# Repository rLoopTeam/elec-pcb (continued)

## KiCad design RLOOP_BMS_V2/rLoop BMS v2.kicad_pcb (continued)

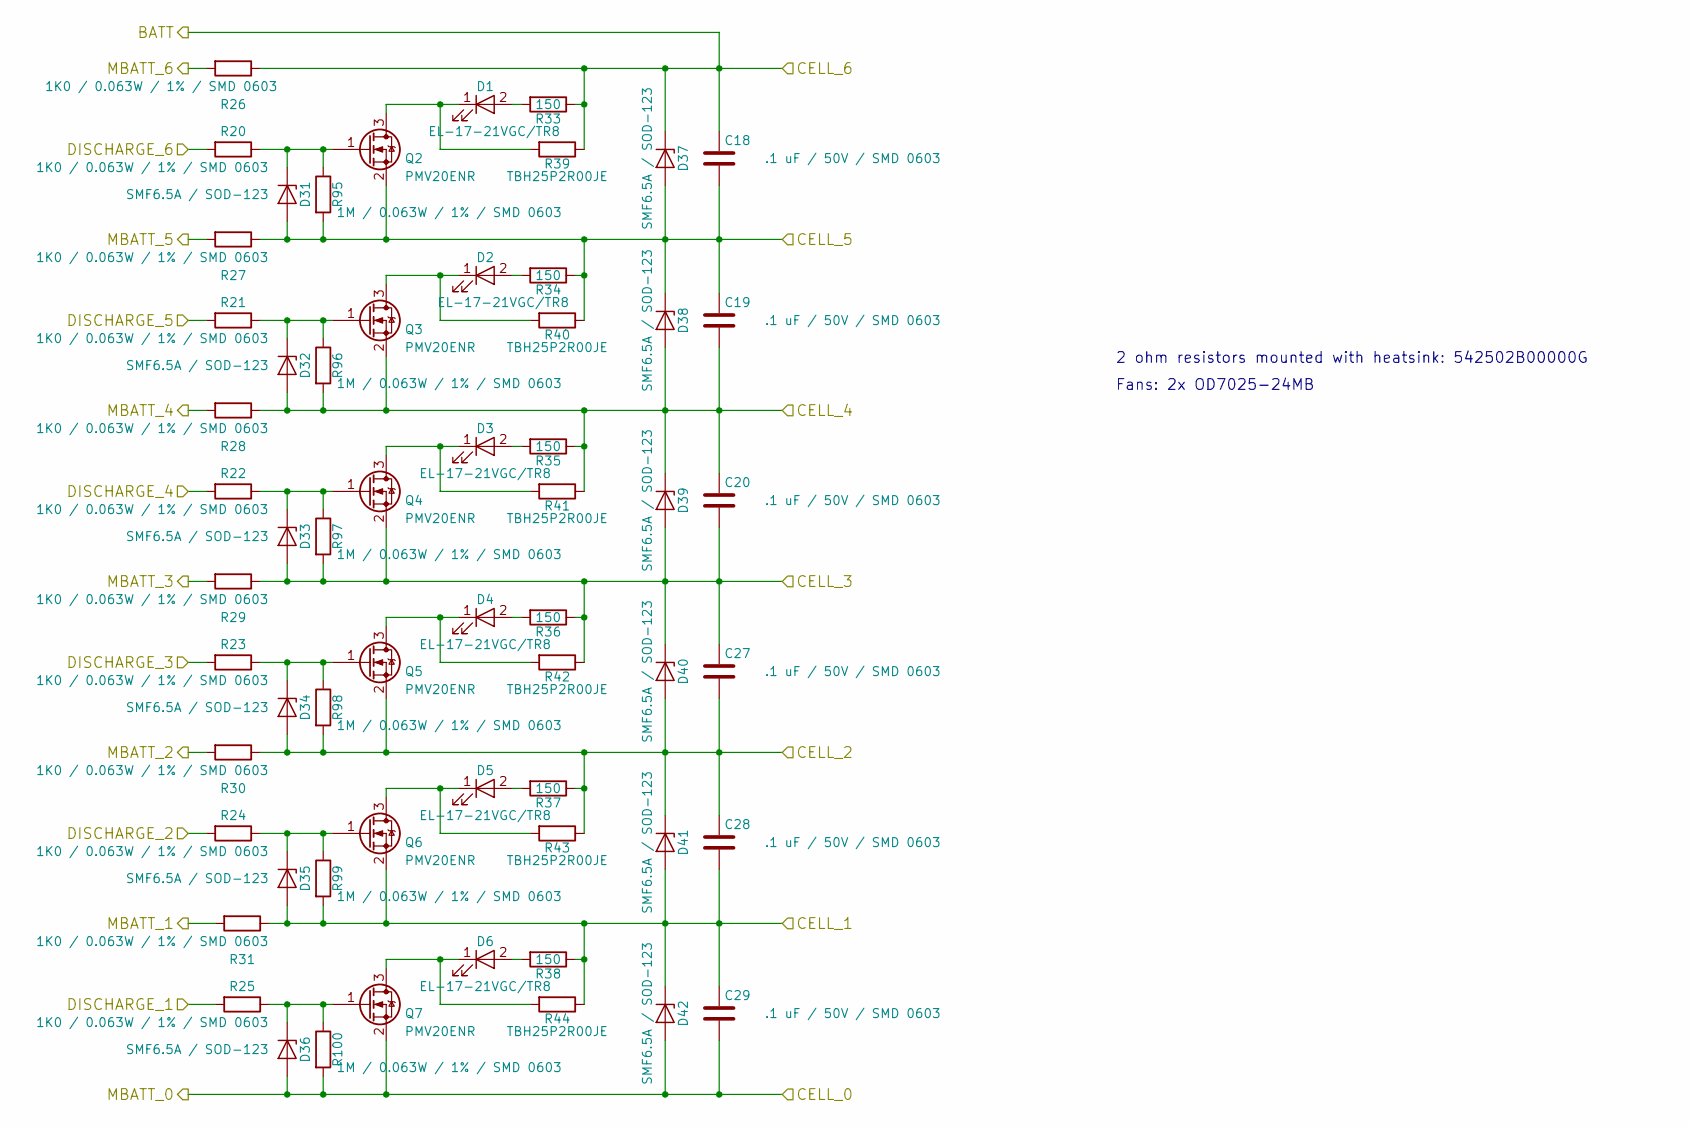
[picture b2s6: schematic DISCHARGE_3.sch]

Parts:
C18, C19, C20, C27, C28, C29: .1 uF / 50V / SMD 0603; C_0603
D1, D2, D3, D4, D5, D6: EL-17-21VGC/TR8; LED_0805
D31, D32, D33, D34, D35, D36, D37, D38, D39, D40, D41, D42: SMF6.5A / SOD-123; D_SOD-123
Q2, Q3, Q4, Q5, Q6, Q7: PMV20ENR; PMV20ENR-TO_236AB
R20, R21, R22, R23, R24, R25, R26, R27, R28, R29, R30, R31: 1K0 / 0.063W / 1% / SMD 0603; R_0603
R33, R34, R35, R36, R37, R38: 150; R_0603
R39, R40, R41, R42, R43, R44: TBH25P2R00JE; 2-OHM-TO-220-TBH25P2R00JE
R95, R96, R97, R98, R99, R100: 1M / 0.063W / 1% / SMD 0603; R_0603

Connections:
/CONTROLLER 3/MBAT2: R31.2; also elsewhere on the board
/CONTROLLER 3/MBAT3: R30.2; also elsewhere on the board
/CONTROLLER 3/MBAT4: R29.2; also elsewhere on the board
/CONTROLLER 3/MBAT5: R28.2; also elsewhere on the board
/CONTROLLER 3/MBAT6: R27.2; also elsewhere on the board
/CONTROLLER 3/MBAT7: R26.2; also elsewhere on the board
/DISCHARGE_3/CELL_1: C28.2, C29.1, D35.2 (A), D41.2 (A), D42.1 (K), Q6.2 (S), R31.1, R38.1, R44.1, R99.2; also elsewhere on the board
/DISCHARGE_3/CELL_2: C27.2, C28.1, D34.2 (A), D40.2 (A), D41.1 (K), Q5.2 (S), R30.1, R37.1, R43.1, R98.2; also elsewhere on the board
/DISCHARGE_3/CELL_3: C20.2, C27.1, D33.2 (A), D39.2 (A), D40.1 (K), Q4.2 (S), R29.1, R36.1, R42.1, R97.2; also elsewhere on the board
/DISCHARGE_3/CELL_4: C19.2, C20.1, D32.2 (A), D38.2 (A), D39.1 (K), Q3.2 (S), R28.1, R35.1, R41.1, R96.2; also elsewhere on the board
/DISCHARGE_3/CELL_5: C18.2, C19.1, D31.2 (A), D37.2 (A), D38.1 (K), Q2.2 (S), R27.1, R34.1, R40.1, R95.2; also elsewhere on the board
/DISCHARGE_3/DISCHARGE_1: R25.2; also elsewhere on the board
/DISCHARGE_3/DISCHARGE_2: R24.2; also elsewhere on the board
/DISCHARGE_3/DISCHARGE_3: R23.2; also elsewhere on the board
/DISCHARGE_3/DISCHARGE_4: R22.2; also elsewhere on the board
/DISCHARGE_3/DISCHARGE_5: R21.2; also elsewhere on the board
/DISCHARGE_3/DISCHARGE_6: R20.2; also elsewhere on the board
GND_3: C29.2, D36.2 (A), D42.2 (A), Q7.2 (S), R100.2; also elsewhere on the board
unnamed: D1.1 (K), Q2.3 (D), R39.2
unnamed: D1.2 (A), R33.2
unnamed: D2.1 (K), Q3.3 (D), R40.2
unnamed: D2.2 (A), R34.2
unnamed: D3.1 (K), Q4.3 (D), R41.2
unnamed: D3.2 (A), R35.2
unnamed: D4.1 (K), Q5.3 (D), R42.2
unnamed: D4.2 (A), R36.2
unnamed: D5.1 (K), Q6.3 (D), R43.2
unnamed: D5.2 (A), R37.2
unnamed: D6.1 (K), Q7.3 (D), R44.2
unnamed: D6.2 (A), R38.2
unnamed: D31.1 (K), Q2.1 (G), R20.1, R95.1
unnamed: D32.1 (K), Q3.1 (G), R21.1, R96.1
unnamed: D33.1 (K), Q4.1 (G), R22.1, R97.1
unnamed: D34.1 (K), Q5.1 (G), R23.1, R98.1
unnamed: D35.1 (K), Q6.1 (G), R24.1, R99.1
unnamed: D36.1 (K), Q7.1 (G), R25.1, R100.1
VDDHV_3: C18.1, D37.1 (K), R26.1, R33.1, R39.1; also elsewhere on the board

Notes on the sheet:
2 ohm resistors mounted with heatsink: 542502B00000G
Fans: 2x OD7025-24MB

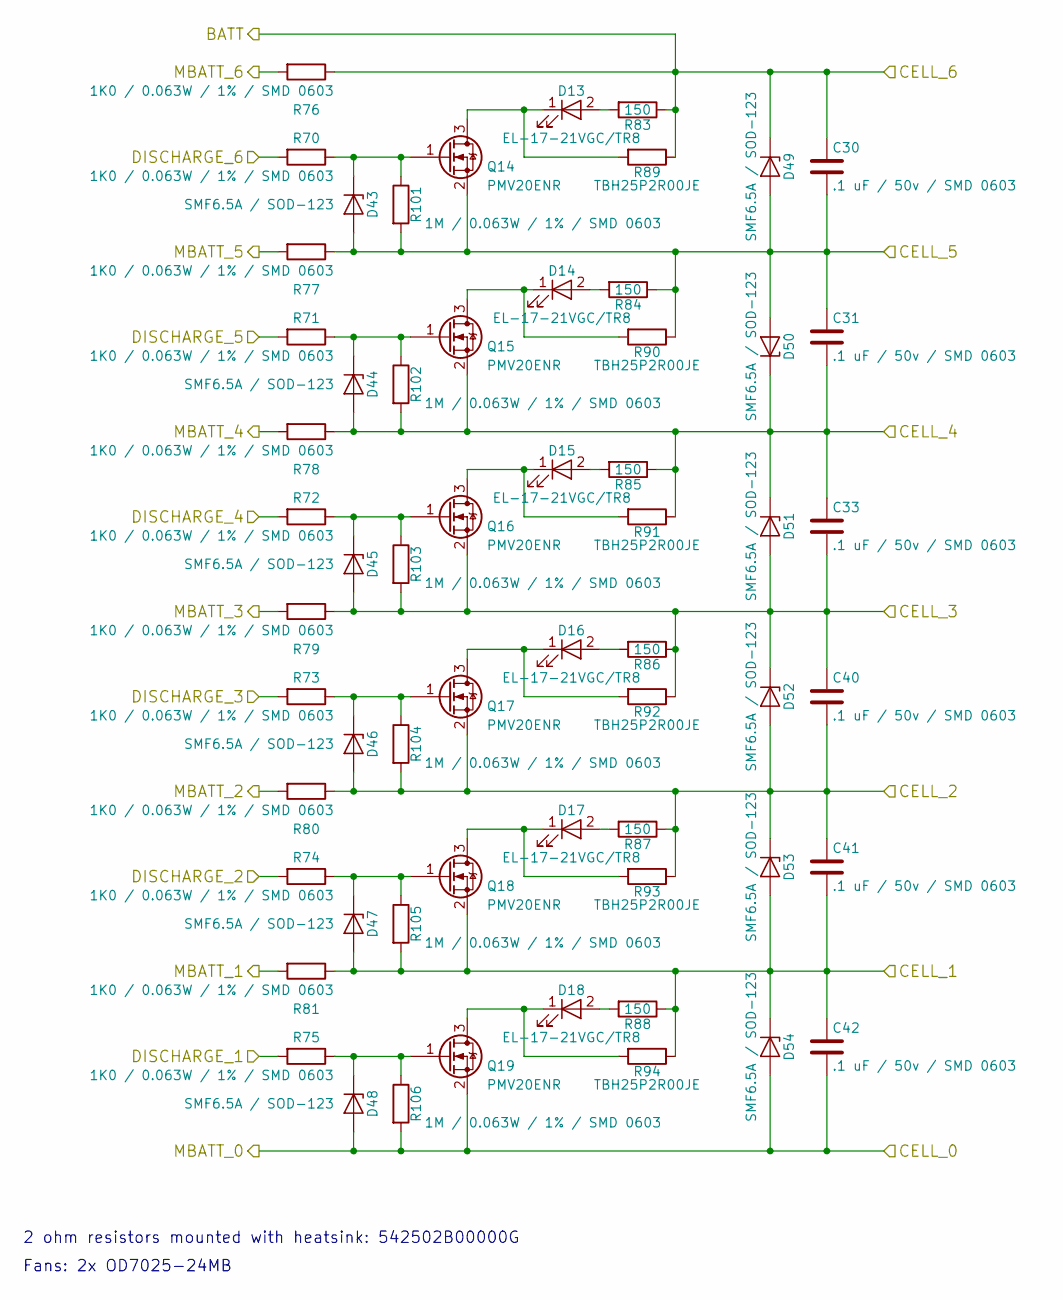
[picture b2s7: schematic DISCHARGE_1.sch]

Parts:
C30, C31, C33, C40, C41, C42: .1 uF / 50v / SMD 0603; C_0603
D13, D14, D15, D16, D17, D18: EL-17-21VGC/TR8; LED_0805
D43, D44, D45, D46, D47, D48, D49, D50, D51, D52, D53, D54: SMF6.5A / SOD-123; D_SOD-123
Q14, Q15, Q16, Q17, Q18, Q19: PMV20ENR; PMV20ENR-TO_236AB
R70, R71, R72, R73, R74, R75, R76, R77, R78, R79, R80, R81: 1K0 / 0.063W / 1% / SMD 0603; R_0603
R83, R84, R85, R86, R87, R88: 150; R_0603
R89, R90, R91, R92, R93, R94: TBH25P2R00JE; 2-OHM-TO-220-TBH25P2R00JE
R101, R102, R103, R104, R105, R106: 1M / 0.063W / 1% / SMD 0603; R_0603

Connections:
/CONTROLLER 1/MBAT2: R81.2; also elsewhere on the board
/CONTROLLER 1/MBAT3: R80.2; also elsewhere on the board
/CONTROLLER 1/MBAT4: R79.2; also elsewhere on the board
/CONTROLLER 1/MBAT5: R78.2; also elsewhere on the board
/CONTROLLER 1/MBAT6: R77.2; also elsewhere on the board
/CONTROLLER 1/MBAT7: R76.2; also elsewhere on the board
/DISCHARGE_1/CELL_1: C41.2, C42.1, D47.2 (A), D53.2 (A), D54.1 (K), Q18.2 (S), R81.1, R88.1, R94.1, R105.2; also elsewhere on the board
/DISCHARGE_1/CELL_2: C40.2, C41.1, D46.2 (A), D52.2 (A), D53.1 (K), Q17.2 (S), R80.1, R87.1, R93.1, R104.2; also elsewhere on the board
/DISCHARGE_1/CELL_3: C33.2, C40.1, D45.2 (A), D51.2 (A), D52.1 (K), Q16.2 (S), R79.1, R86.1, R92.1, R103.2; also elsewhere on the board
/DISCHARGE_1/CELL_4: C31.2, C33.1, D44.2 (A), D50.1 (K), D51.1 (K), Q15.2 (S), R78.1, R85.1, R91.1, R102.2; also elsewhere on the board
/DISCHARGE_1/CELL_5: C30.2, C31.1, D43.2 (A), D49.2 (A), D50.2 (A), Q14.2 (S), R77.1, R84.1, R90.1, R101.2; also elsewhere on the board
/DISCHARGE_1/DISCHARGE_1: R75.2; also elsewhere on the board
/DISCHARGE_1/DISCHARGE_2: R74.2; also elsewhere on the board
/DISCHARGE_1/DISCHARGE_3: R73.2; also elsewhere on the board
/DISCHARGE_1/DISCHARGE_4: R72.2; also elsewhere on the board
/DISCHARGE_1/DISCHARGE_5: R71.2; also elsewhere on the board
/DISCHARGE_1/DISCHARGE_6: R70.2; also elsewhere on the board
GND_1: C42.2, D48.2 (A), D54.2 (A), Q19.2 (S), R106.2; also elsewhere on the board
GND_2: C30.1, D49.1 (K), R76.1, R83.1, R89.1; also elsewhere on the board
unnamed: D13.1 (K), Q14.3 (D), R89.2
unnamed: D13.2 (A), R83.2
unnamed: D14.1 (K), Q15.3 (D), R90.2
unnamed: D14.2 (A), R84.2
unnamed: D15.1 (K), Q16.3 (D), R91.2
unnamed: D15.2 (A), R85.2
unnamed: D16.1 (K), Q17.3 (D), R92.2
unnamed: D16.2 (A), R86.2
unnamed: D17.1 (K), Q18.3 (D), R93.2
unnamed: D17.2 (A), R87.2
unnamed: D18.1 (K), Q19.3 (D), R94.2
unnamed: D18.2 (A), R88.2
unnamed: D43.1 (K), Q14.1 (G), R70.1, R101.1
unnamed: D44.1 (K), Q15.1 (G), R71.1, R102.1
unnamed: D45.1 (K), Q16.1 (G), R72.1, R103.1
unnamed: D46.1 (K), Q17.1 (G), R73.1, R104.1
unnamed: D47.1 (K), Q18.1 (G), R74.1, R105.1
unnamed: D48.1 (K), Q19.1 (G), R75.1, R106.1

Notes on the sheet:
2 ohm resistors mounted with heatsink: 542502B00000G
Fans: 2x OD7025-24MB

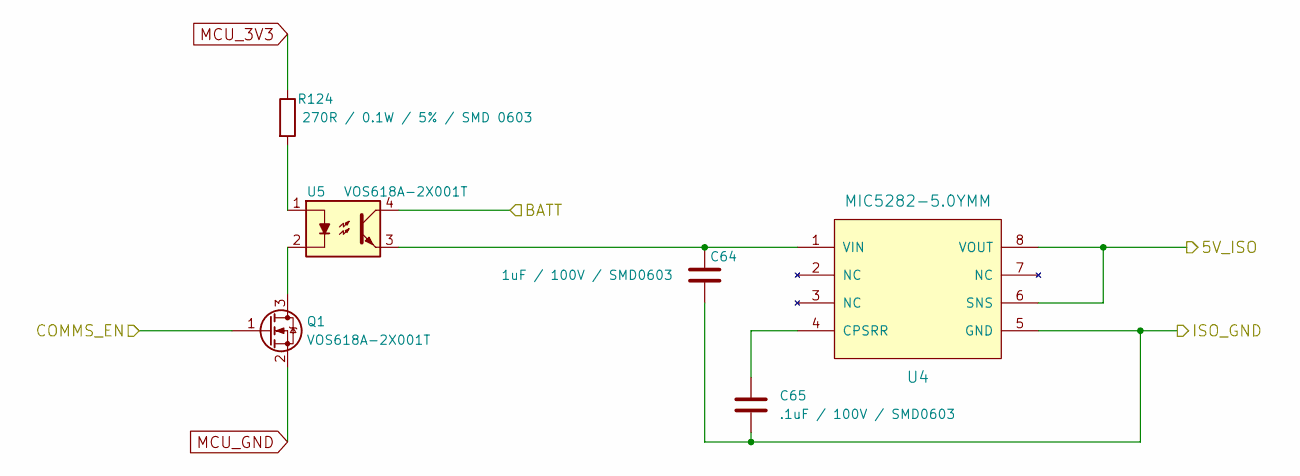
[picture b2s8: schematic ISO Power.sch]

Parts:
C64: 1uF / 100V / SMD0603; C_0603
C65: .1uF / 100V / SMD0603; C_0603
Q1: VOS618A-2X001T; SuperSOT-3
R124: 270R / 0.1W / 5% / SMD 0603; R_0603
U4: MIC5282-5.0YMM; MIC5282
U5: VOS618A-2X001T

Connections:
/ISO POWER/5V_ISO: U4.6 (SNS), U4.8 (VOUT); also elsewhere on the board
/ISO POWER/COMMS_EN: Q1.1 (G); also elsewhere on the board
GND_1: C64.2, C65.2, U4.5 (GND); also elsewhere on the board
MCU_3V3: R124.1; also elsewhere on the board
MCU_GND: Q1.2 (S); also elsewhere on the board
unnamed: C64.1, U4.1 (VIN), U5.3
unnamed: C65.1, U4.4 (CPSRR)
unnamed: Q1.3 (D), U5.2
unnamed: R124.2, U5.1
VDDHV_3: U5.4; also elsewhere on the board

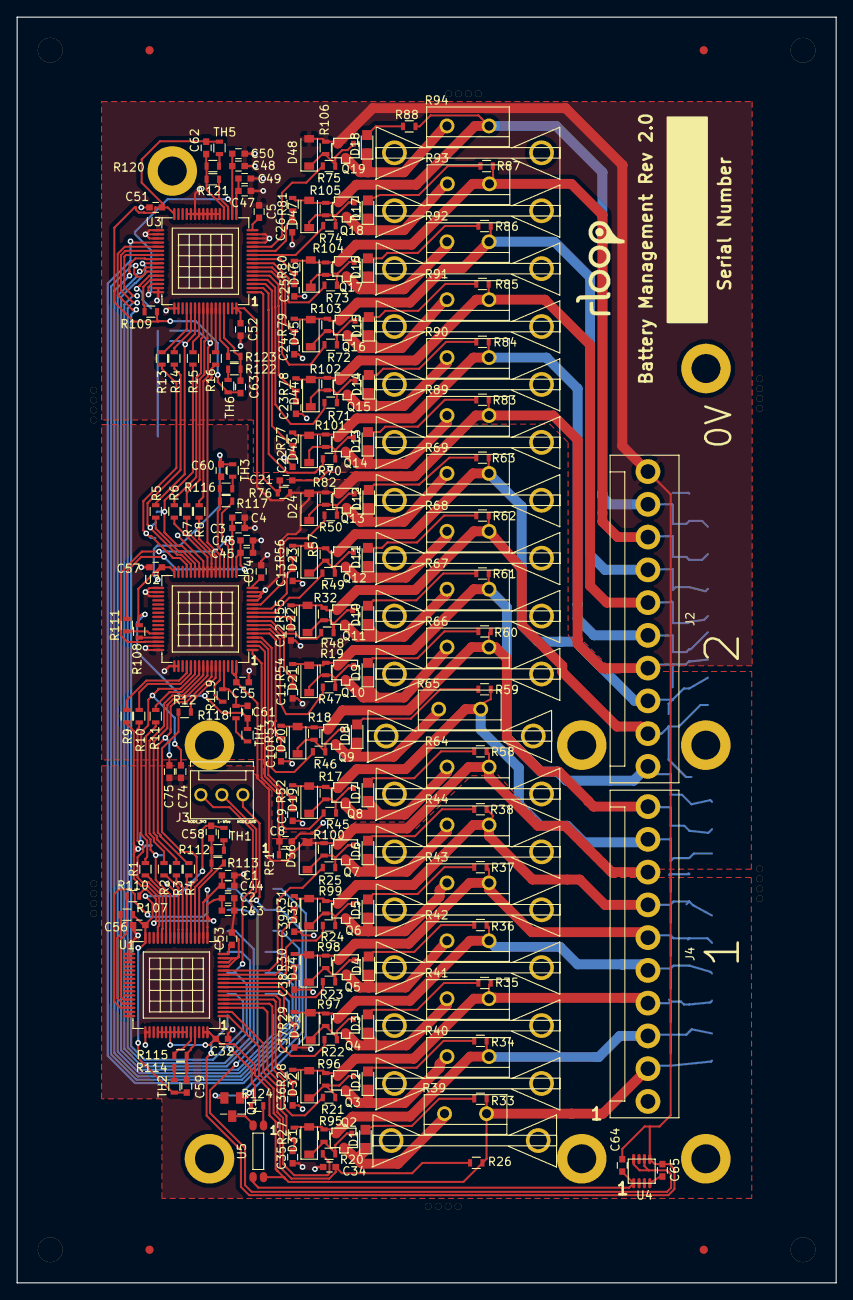
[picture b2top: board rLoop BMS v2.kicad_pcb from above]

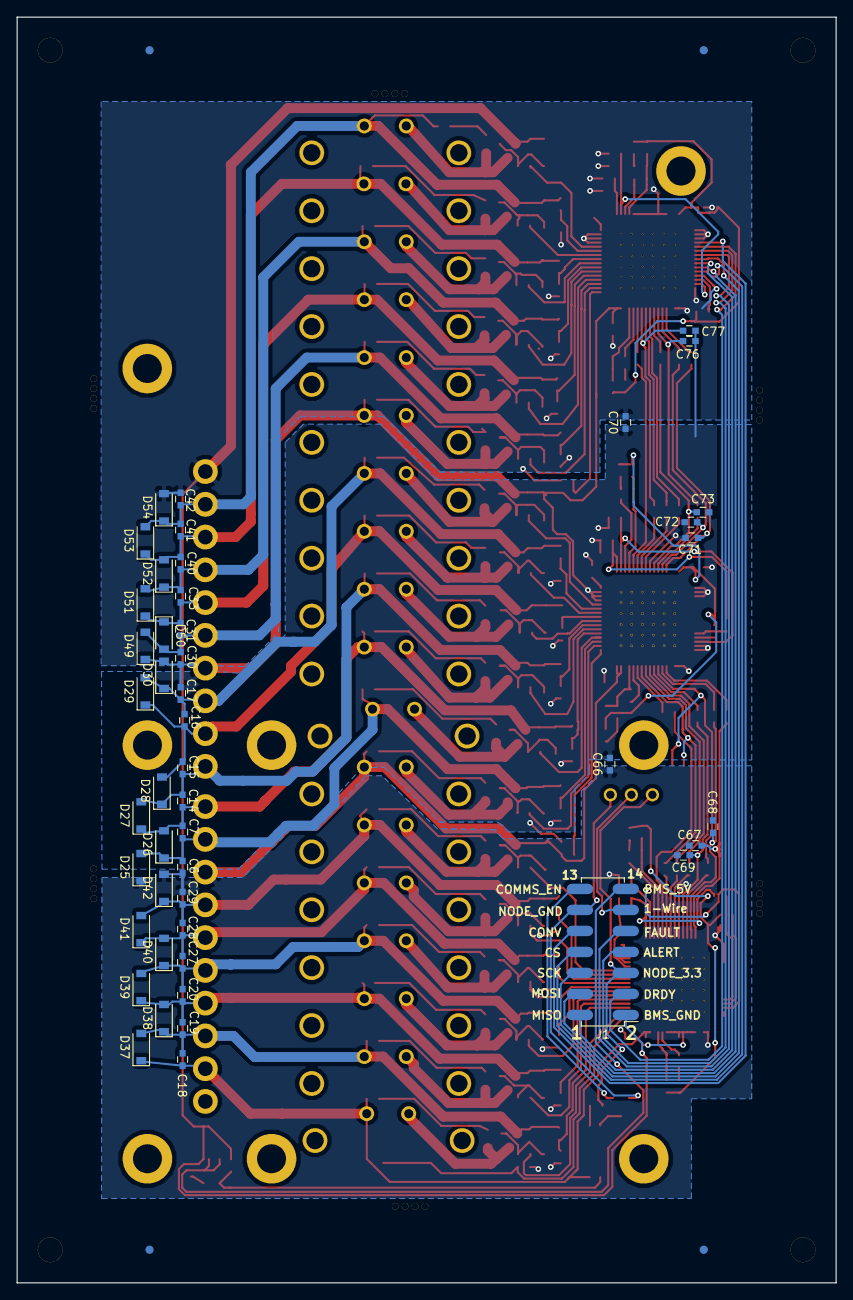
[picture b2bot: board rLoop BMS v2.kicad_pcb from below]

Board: 2 copper layers, 99.0 x 153.0 mm, 289 parts (47 on the bottom side), 193 nets.

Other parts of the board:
J4: 1-640445-0

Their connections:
/DISCHARGE_2/CELL_4: J4.1; also elsewhere on the board
/DISCHARGE_2/CELL_5: J4.2; also elsewhere on the board
/DISCHARGE_3/CELL_1: J4.4; also elsewhere on the board
/DISCHARGE_3/CELL_2: J4.5; also elsewhere on the board
/DISCHARGE_3/CELL_3: J4.6; also elsewhere on the board
/DISCHARGE_3/CELL_4: J4.7; also elsewhere on the board
/DISCHARGE_3/CELL_5: J4.8; also elsewhere on the board
GND_3: J4.3; also elsewhere on the board
VDDHV_3: J4.9; also elsewhere on the board

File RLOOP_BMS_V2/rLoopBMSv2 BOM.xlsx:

Reference | Value
C1,3,43,45,47-48,51,56,57 | 2.2 uF / 50V/ 10% / SMD 0603
C2,4,6,7,8-20,21-42,44,46,49,50,52,55,65 | .1 uF / 50v / SMD 0603
C5,53,54 | 10 uF / 10V/ 10% / SMD 0603
C58-63 | .047 uF / 50V/ 10% / SMD 0603
C64 | 1uF / 100V / SMD0603
C66-77 | 3.3 nF / 50V/ 10% / SMD 0603
D1-18 | EL-17-21VGC/TR8
D19-54 | SMF6.5A / SOD-123
Q1 | FDN337N
Q2-19 | PMV20ENR
J1 | 1241050-7
J2 | TE 2-640387-0
J3 | TE 2-292161-3
R1-16,20-31,45-46,70-81 | 1K0 / 0.063W / 1% / SMD 0603
R17-19,32,57,82,95-106 | 1M / .063W / 1% / SMD 0603
R33-38,58-63,83-88 | 150 / 0.1W / 10% / SMD 0603
R39-44,64-69,89-94 | TBH25P2R00JE
R107-111 | 100K0 / 0.063W / 5% / SMD 0603
R112-123 | 1.47k / 0.063W / 1% / SMD 0603
R124 | 270R / 0.1W / 5% / SMD 0603
TH1-6 | 10k / 1% / 3454K / SMD 0603
U1-3 | bq76PL536A_HTQFP
U4 | MIC5282-5.0YMM
U5 | VOS618A-2X001T
 | Heatsink: 542502B00000G x16
 | Fanx: 2x 0D7025-24MB x2

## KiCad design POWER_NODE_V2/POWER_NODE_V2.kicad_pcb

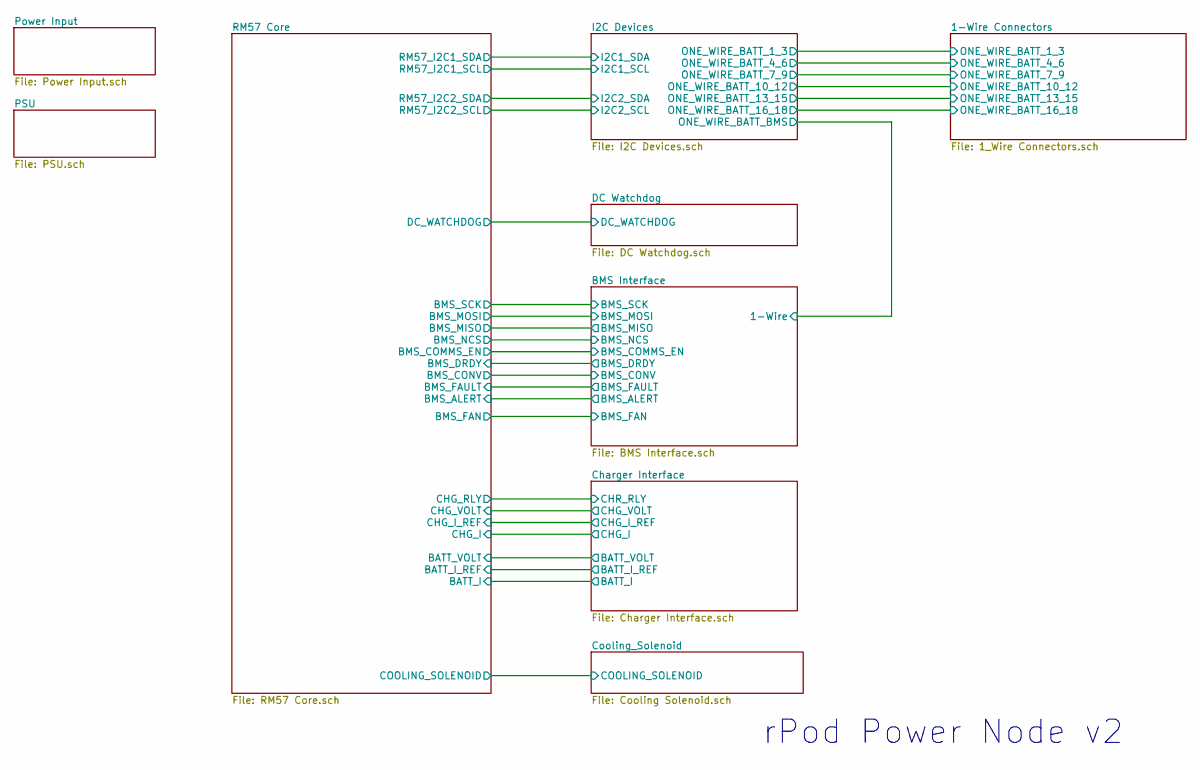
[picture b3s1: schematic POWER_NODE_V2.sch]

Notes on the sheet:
rPod Power Node v2

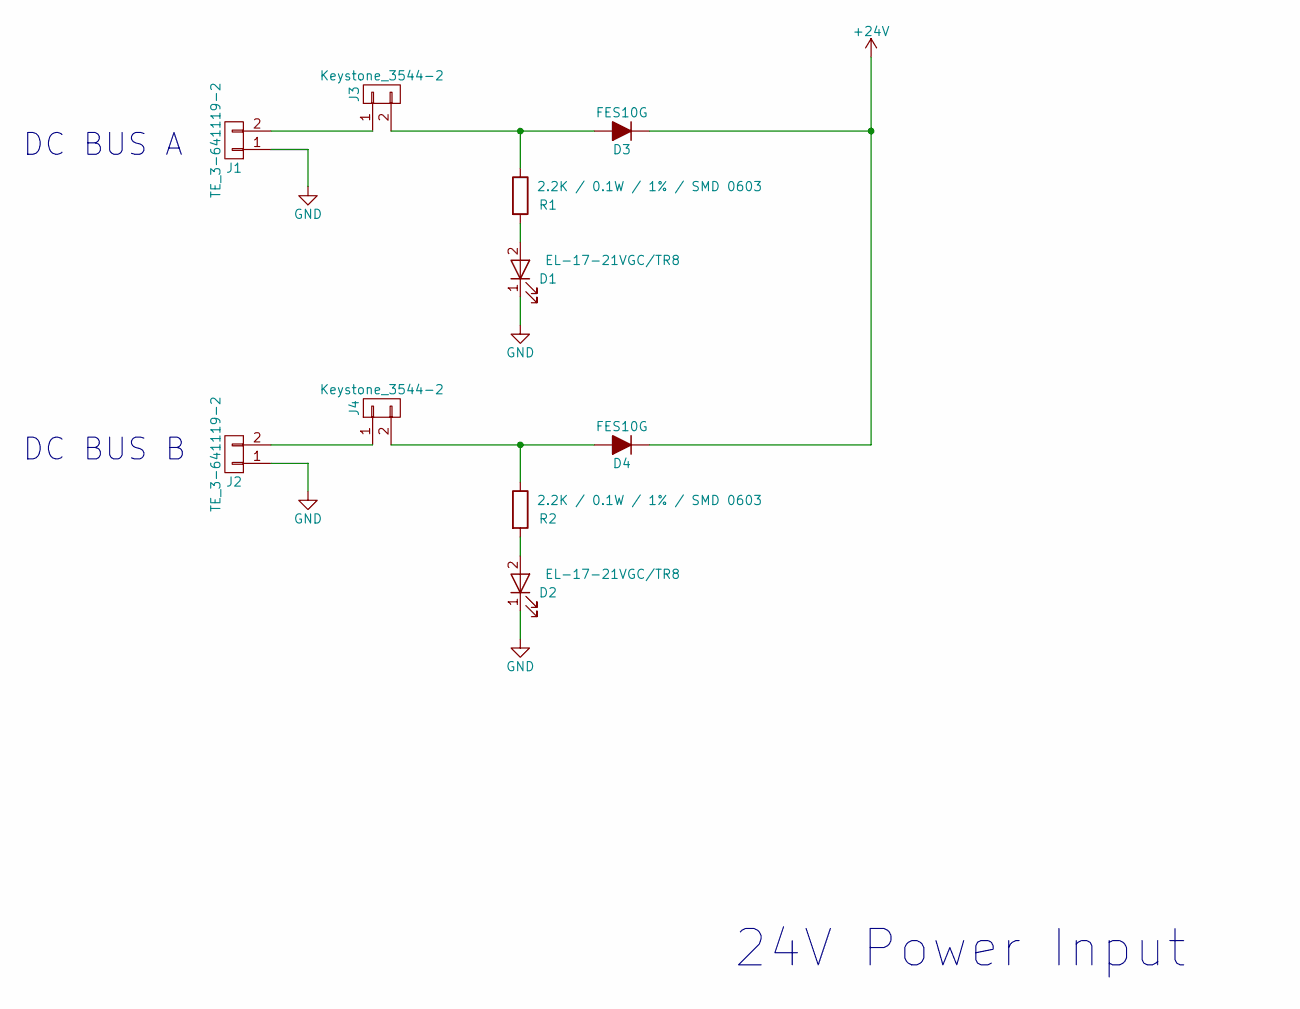
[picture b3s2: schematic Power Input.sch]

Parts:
D1, D2: EL-17-21VGC/TR8; LED_0805
D3, D4: FES10G; TO-277A_SMPC
J1, J2: TE_3-641119-2; 3-641119-2_TE_2P_MTA156_HDR
J3, J4: Keystone_3544-2
R1, R2: 2.2K / 0.1W / 1% / SMD 0603; R_0603

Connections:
+24V: D3.1 (K), D4.1 (K); also elsewhere on the board
GND: D1.1 (K), D2.1 (K), J1.1, J2.1; also elsewhere on the board
unnamed: D1.2 (A), R1.2
unnamed: D2.2 (A), R2.2
unnamed: D3.2 (A), J3.2, R1.1
unnamed: D4.2 (A), J4.2, R2.1
unnamed: J1.2, J3.1
unnamed: J2.2, J4.1

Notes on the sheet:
24V Power Input
DC BUS A
DC BUS B

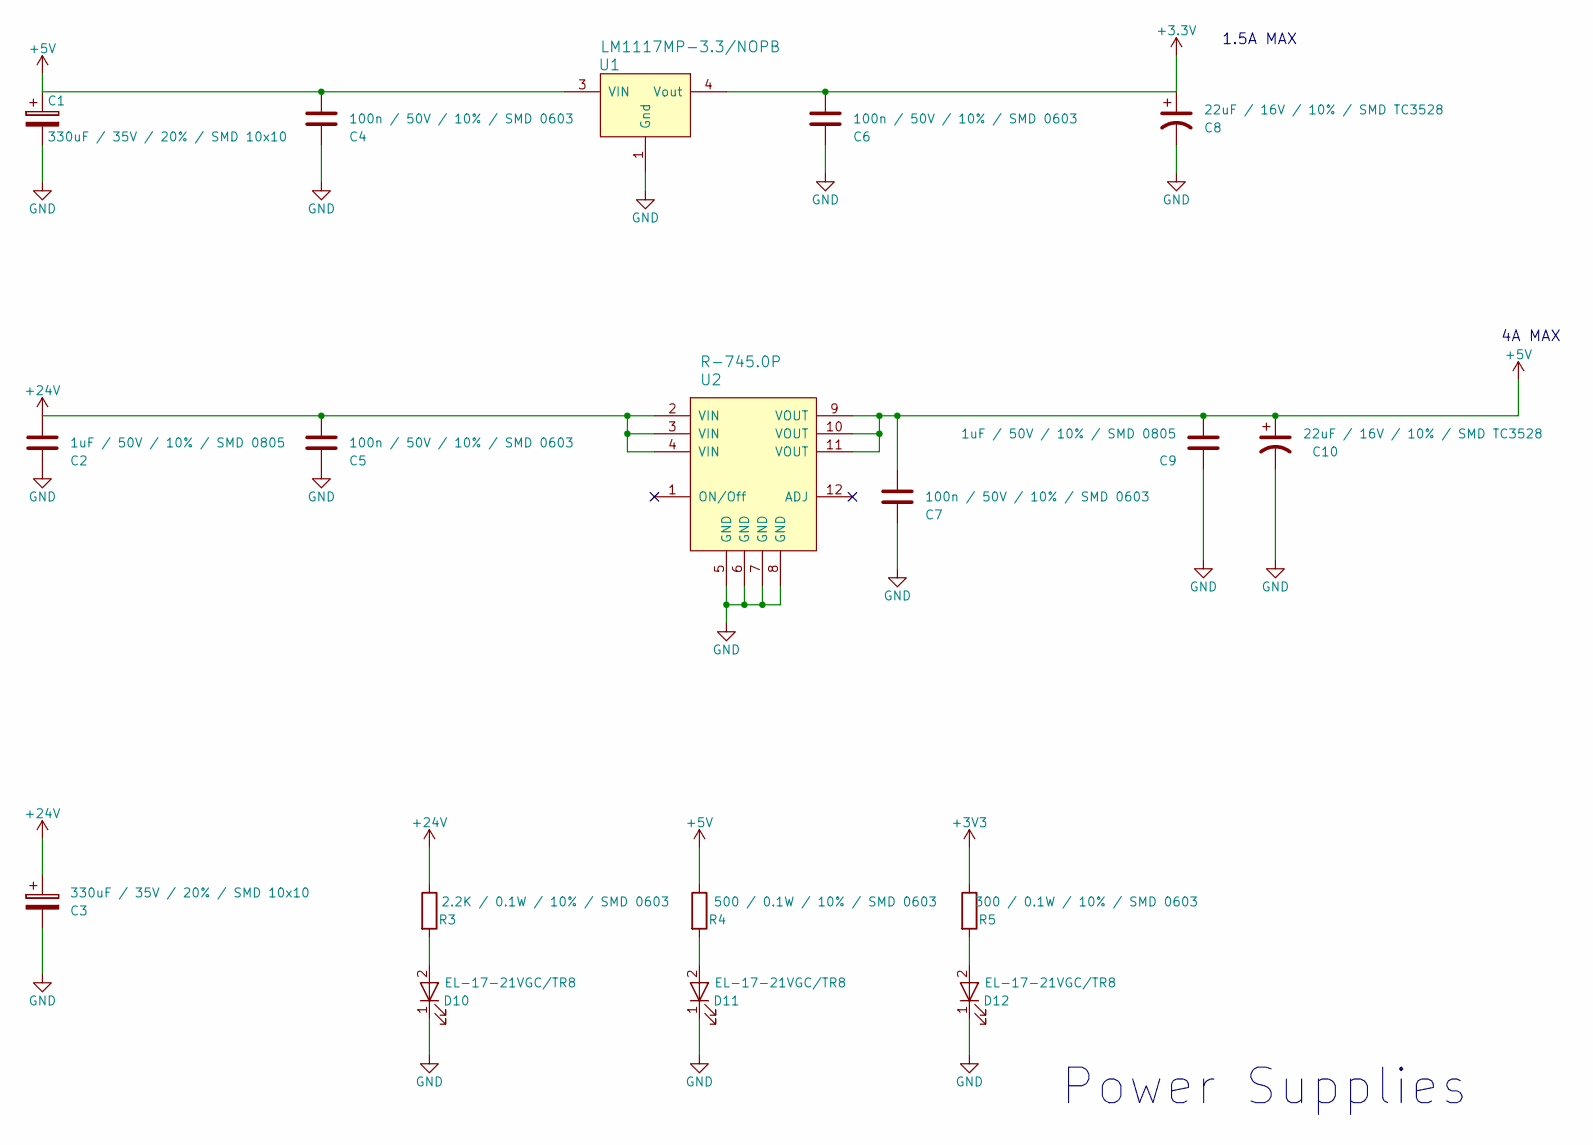
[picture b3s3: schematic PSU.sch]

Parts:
C1, C3: 330uF / 35V / 20% / SMD 10x10; CP_Elec_10x10
C2, C9: 1uF / 50V / 10% / SMD 0805; C_0805
C4, C5, C6, C7: 100n / 50V / 10% / SMD 0603; C_0603
C8, C10: 22uF / 16V / 10% / SMD TC3528; CP_Tantalum_Case-T_EIA-3528-12_Reflow
D10, D11, D12: EL-17-21VGC/TR8; LED_0805
R3: 2.2K / 0.1W / 10% / SMD 0603; R_0603
R4: 500 / 0.1W / 10% / SMD 0603; R_0603
R5: 300 / 0.1W / 10% / SMD 0603; R_0603
U1: LM1117MP-3.3/NOPB; SOT-223
U2: R-745.0P

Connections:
+5V: C1.1, C4.1, C7.1, C9.1, C10.1, R4.1, U1.3 (VIN), U2.9 (VOUT), U2.10 (VOUT), U2.11 (VOUT); also elsewhere on the board
+24V: C2.1, C3.1, C5.1, R3.1, U2.2 (VIN), U2.3 (VIN), U2.4 (VIN); also elsewhere on the board
GND: C1.2, C2.2, C3.2, C4.2, C5.2, C6.2, C7.2, C8.2, C9.2, C10.2, D10.1 (K), D11.1 (K), D12.1 (K), U1.1 (Gnd), U2.5 (GND), U2.6 (GND), U2.7 (GND), U2.8 (GND); also elsewhere on the board
unnamed: D10.2 (A), R3.2
unnamed: D11.2 (A), R4.2
unnamed: D12.2 (A), R5.2

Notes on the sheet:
1.5A MAX
4A MAX
Power Supplies

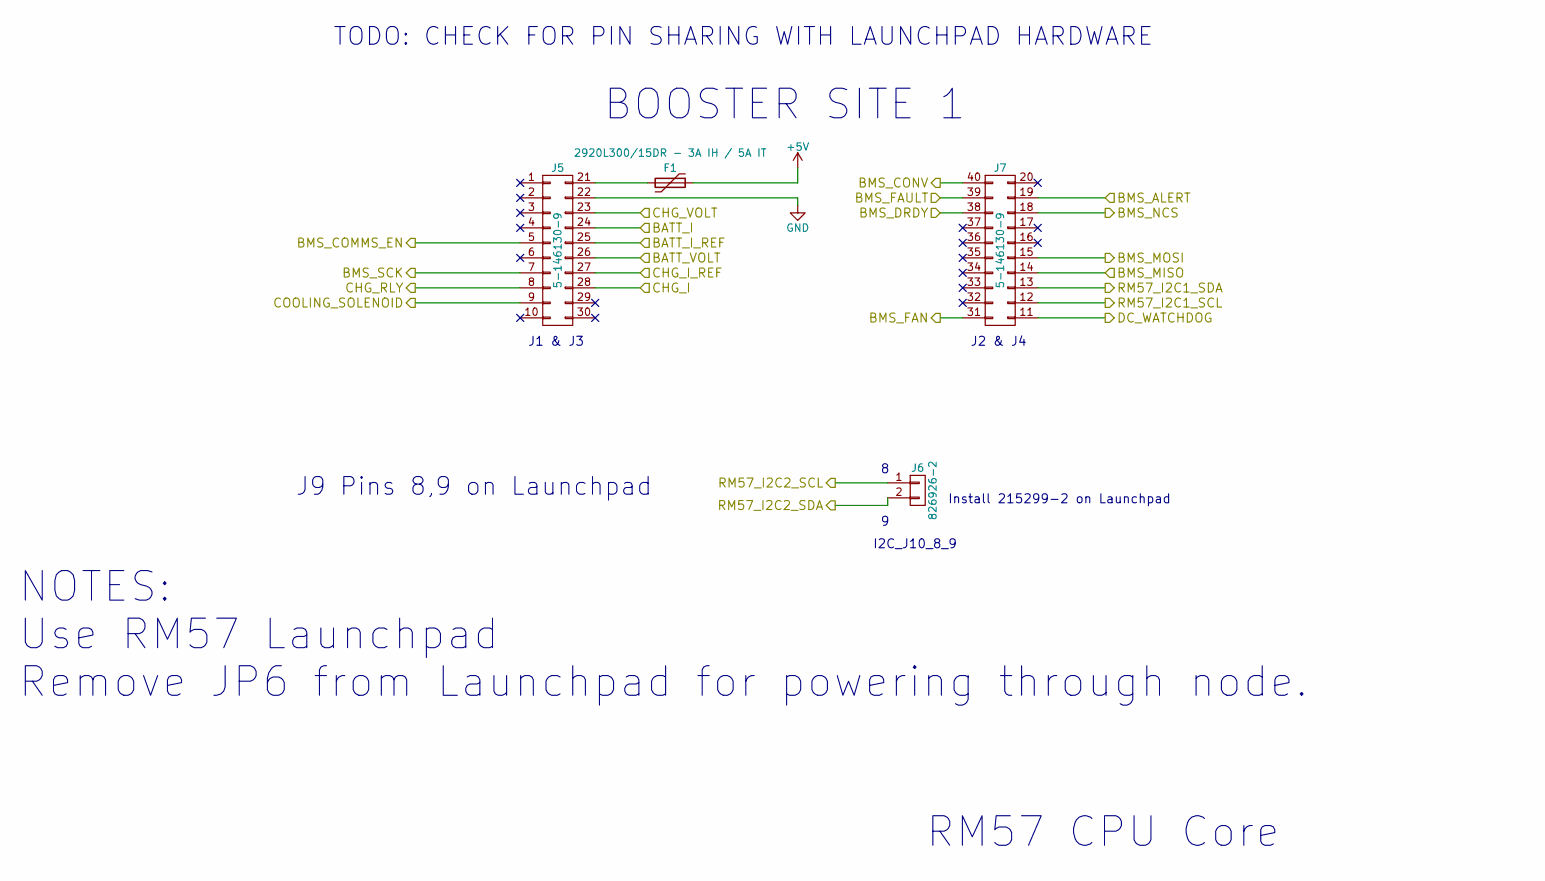
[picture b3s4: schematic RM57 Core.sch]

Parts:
F1: 2920L300/15DR - 3A IH / 5A IT; 2920L300_15DR
J5: 5-146130-9; Booster1_Header_J1_J3
J6: 826926-2; Pin_Header_Straight_1x02_Pitch2.54mm
J7: 5-146130-9; Booster1_J4_J2

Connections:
+5V: F1.1; also elsewhere on the board
/BMS Interface/BMS_ALERT: J7.19; also elsewhere on the board
/BMS Interface/BMS_COMMS_EN: J5.5; also elsewhere on the board
/BMS Interface/BMS_CONV: J7.40; also elsewhere on the board
/BMS Interface/BMS_DRDY: J7.38; also elsewhere on the board
/BMS Interface/BMS_FAN: J7.31; also elsewhere on the board
/BMS Interface/BMS_FAULT: J7.39; also elsewhere on the board
/BMS Interface/BMS_MISO: J7.14; also elsewhere on the board
/BMS Interface/BMS_MOSI: J7.15; also elsewhere on the board
/BMS Interface/BMS_NCS: J7.18; also elsewhere on the board
/BMS Interface/BMS_SCK: J5.7; also elsewhere on the board
/Charger Interface/BATT_I: J5.24; also elsewhere on the board
/Charger Interface/BATT_I_REF: J5.25; also elsewhere on the board
/Charger Interface/BATT_VOLT: J5.26; also elsewhere on the board
/Charger Interface/CHG_I: J5.28; also elsewhere on the board
/Charger Interface/CHG_I_REF: J5.27; also elsewhere on the board
/Charger Interface/CHG_VOLT: J5.23; also elsewhere on the board
/Cooling_Solenoid/COOLING_SOLENOID: J5.9; also elsewhere on the board
/DC Watchdog/DC_WATCHDOG: J7.11; also elsewhere on the board
/I2C Devices/I2C1_SCL: J7.12; also elsewhere on the board
/I2C Devices/I2C1_SDA: J7.13; also elsewhere on the board
/I2C Devices/I2C2_SCL: J6.1; also elsewhere on the board
/I2C Devices/I2C2_SDA: J6.2; also elsewhere on the board
/RM57 Core/CHG_RLY: J5.8; also elsewhere on the board
GND: J5.22; also elsewhere on the board
unnamed: F1.2, J5.21

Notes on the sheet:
TODO: CHECK FOR PIN SHARING WITH LAUNCHPAD HARDWARE
RM57 CPU Core
NOTES: Use RM57 Launchpad Remove JP6 from Launchpad for powering through node.
BOOSTER SITE 1
J9 Pins 8,9 on Launchpad
J1 & J3
J2 & J4
I2C_J10_8_9
Install 215299-2 on Launchpad

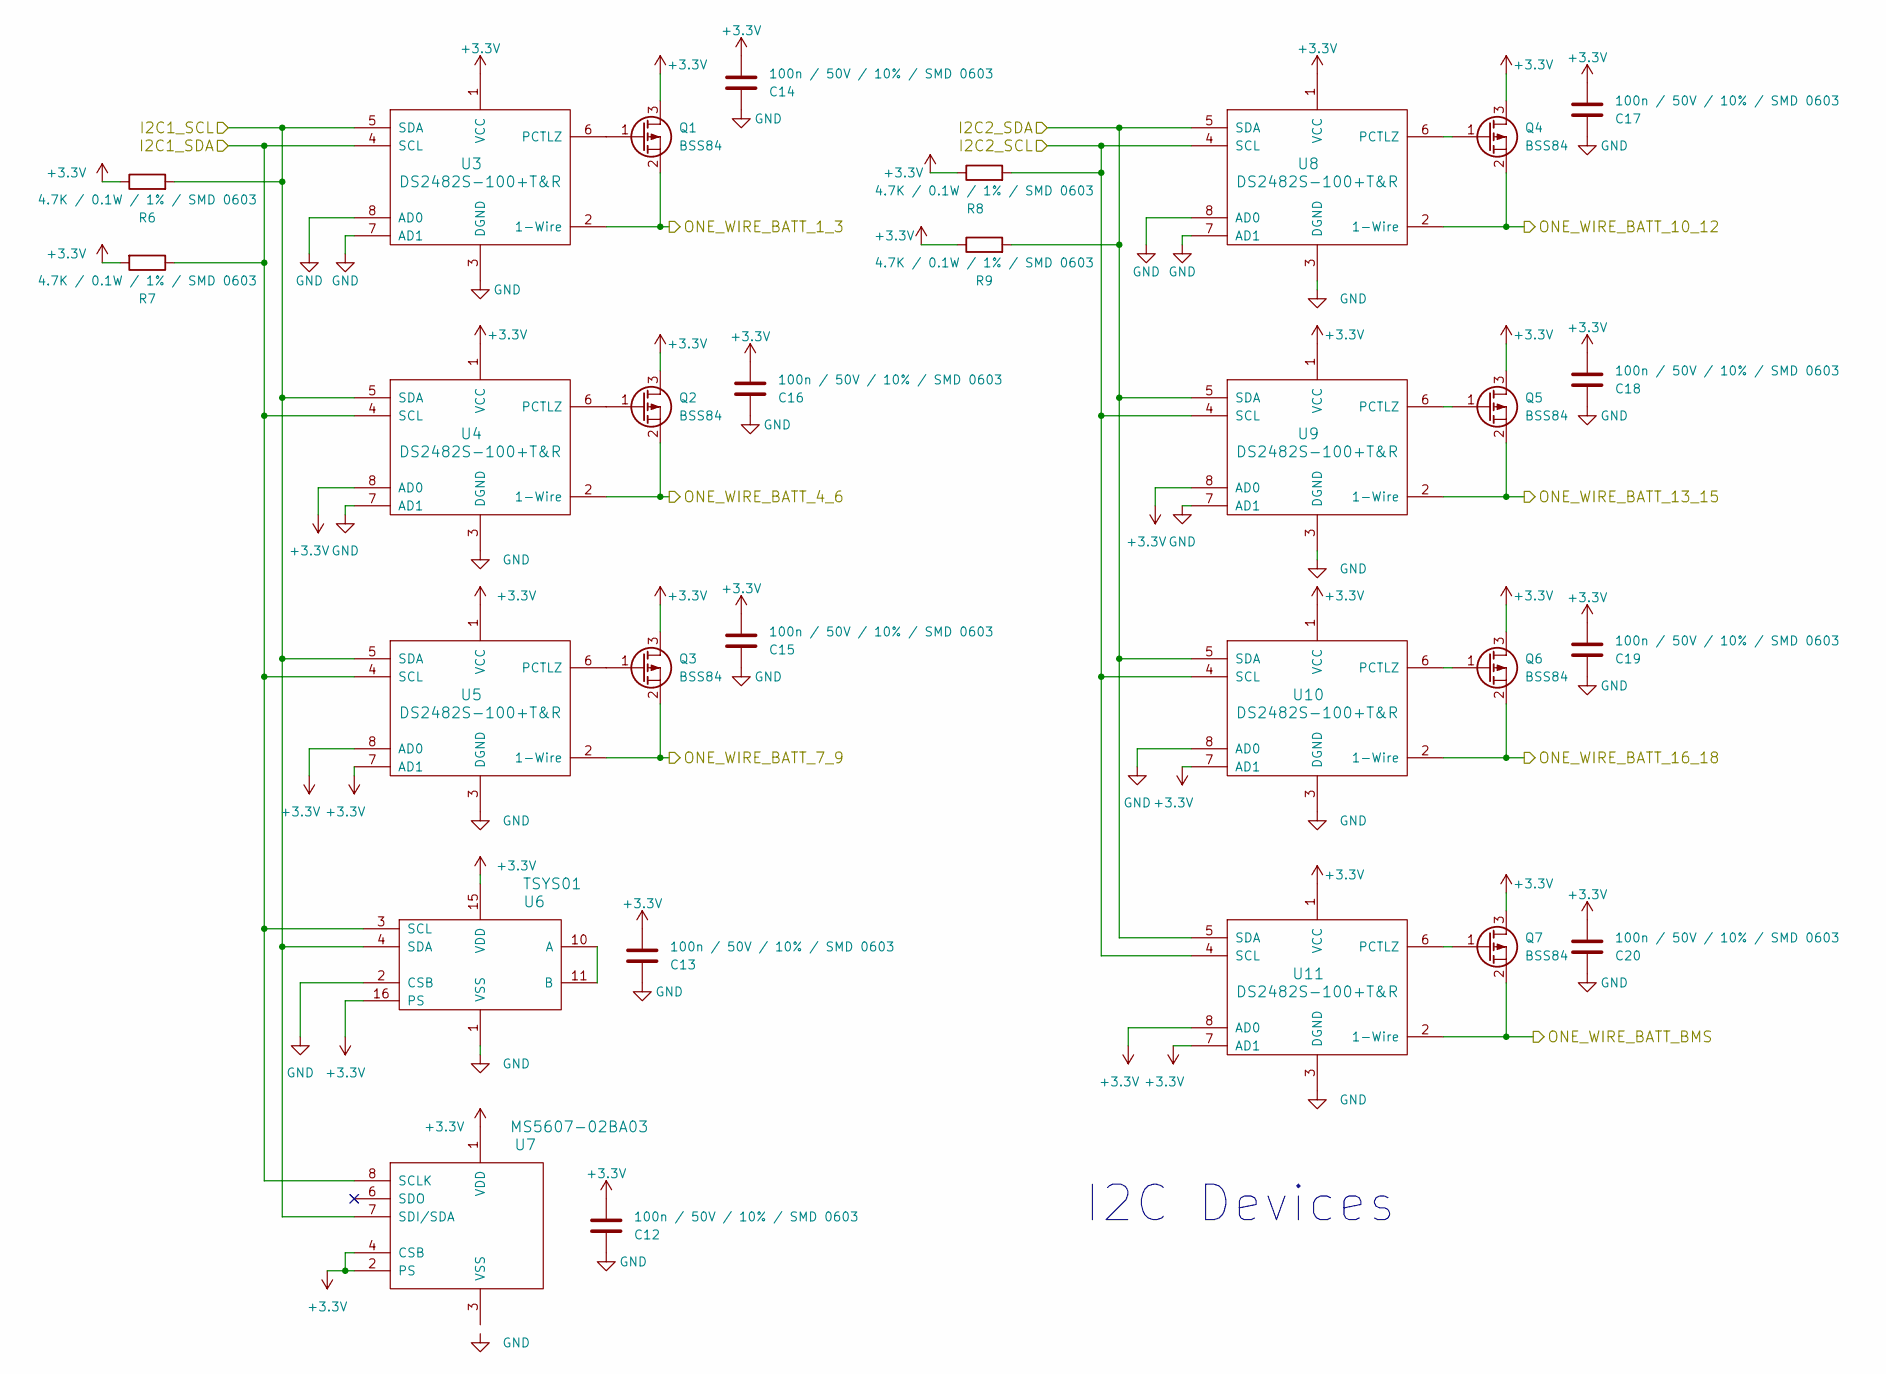
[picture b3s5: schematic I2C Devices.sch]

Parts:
C12, C13, C14, C15, C16, C17, C18, C19, C20: 100n / 50V / 10% / SMD 0603; C_0603
Q1, Q2, Q3, Q4, Q5, Q6, Q7: BSS84; SOT-23
R6, R7, R8, R9: 4.7K / 0.1W / 1% / SMD 0603; R_0603
U3, U4, U5, U8, U9, U10, U11: DS2482S-100+T&R; SOIC-8-N
U6: TSYS01; QFN16_4x4
U7: MS5607-02BA03; ms5607-02ba03

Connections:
/1-Wire Connectors/ONE_WIRE_BATT_1_3: Q1.2 (S), U3.2 (1-Wire); also elsewhere on the board
/1-Wire Connectors/ONE_WIRE_BATT_4_6: Q2.2 (S), U4.2 (1-Wire); also elsewhere on the board
/1-Wire Connectors/ONE_WIRE_BATT_7_9: Q3.2 (S), U5.2 (1-Wire); also elsewhere on the board
/1-Wire Connectors/ONE_WIRE_BATT_10_12: Q4.2 (S), U8.2 (1-Wire); also elsewhere on the board
/1-Wire Connectors/ONE_WIRE_BATT_13_15: Q5.2 (S), U9.2 (1-Wire); also elsewhere on the board
/1-Wire Connectors/ONE_WIRE_BATT_16_18: Q6.2 (S), U10.2 (1-Wire); also elsewhere on the board
/BMS Interface/1-Wire: Q7.2 (S), U11.2 (1-Wire); also elsewhere on the board
/I2C Devices/I2C1_SCL: R6.2, U3.5 (SDA), U4.5 (SDA), U5.5 (SDA), U6.4 (SDA), U7.7 (SDI/SDA); also elsewhere on the board
/I2C Devices/I2C1_SDA: R7.1, U3.4 (SCL), U4.4 (SCL), U5.4 (SCL), U6.3 (SCL), U7.8 (SCLK); also elsewhere on the board
/I2C Devices/I2C2_SCL: R8.2, U8.4 (SCL), U9.4 (SCL), U10.4 (SCL), U11.4 (SCL); also elsewhere on the board
/I2C Devices/I2C2_SDA: R9.2, U8.5 (SDA), U9.5 (SDA), U10.5 (SDA), U11.5 (SDA); also elsewhere on the board
GND: C12.2, C13.2, C14.2, C15.2, C16.2, C17.2, C18.2, C19.2, C20.2, U3.3 (DGND), U3.7 (AD1), U3.8 (AD0), U4.3 (DGND), U4.7 (AD1), U5.3 (DGND), U6.1 (VSS), U6.2 (CSB), U8.3 (DGND), U8.7 (AD1), U8.8 (AD0), U9.3 (DGND), U9.7 (AD1), U10.3 (DGND), U10.8 (AD0), U11.3 (DGND); also elsewhere on the board
unnamed: Q1.1 (G), U3.6 (PCTLZ)
unnamed: Q2.1 (G), U4.6 (PCTLZ)
unnamed: Q3.1 (G), U5.6 (PCTLZ)
unnamed: Q4.1 (G), U8.6 (PCTLZ)
unnamed: Q5.1 (G), U9.6 (PCTLZ)
unnamed: Q6.1 (G), U10.6 (PCTLZ)
unnamed: Q7.1 (G), U11.6 (PCTLZ)
unnamed: U6.10 (A), U6.11 (B)

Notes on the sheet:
I2C Devices
